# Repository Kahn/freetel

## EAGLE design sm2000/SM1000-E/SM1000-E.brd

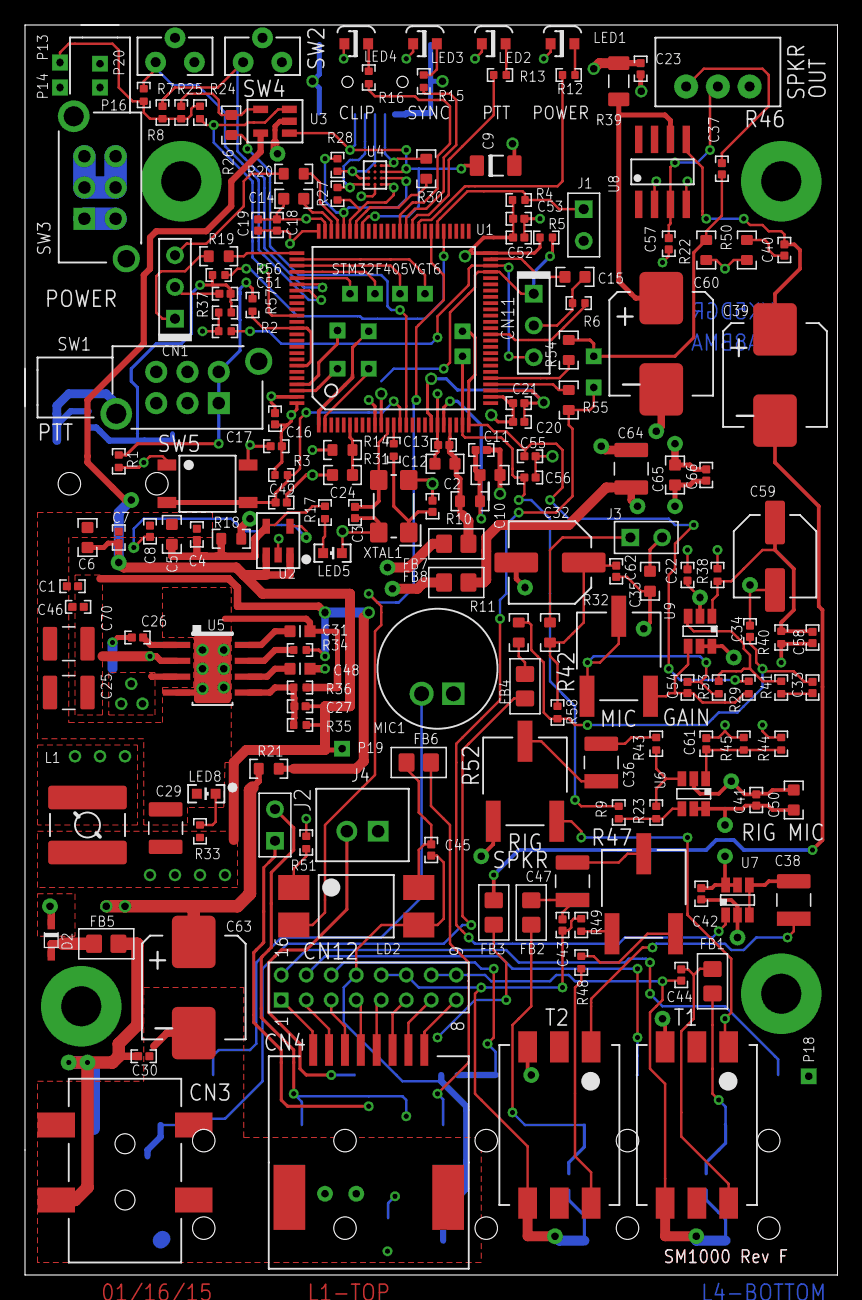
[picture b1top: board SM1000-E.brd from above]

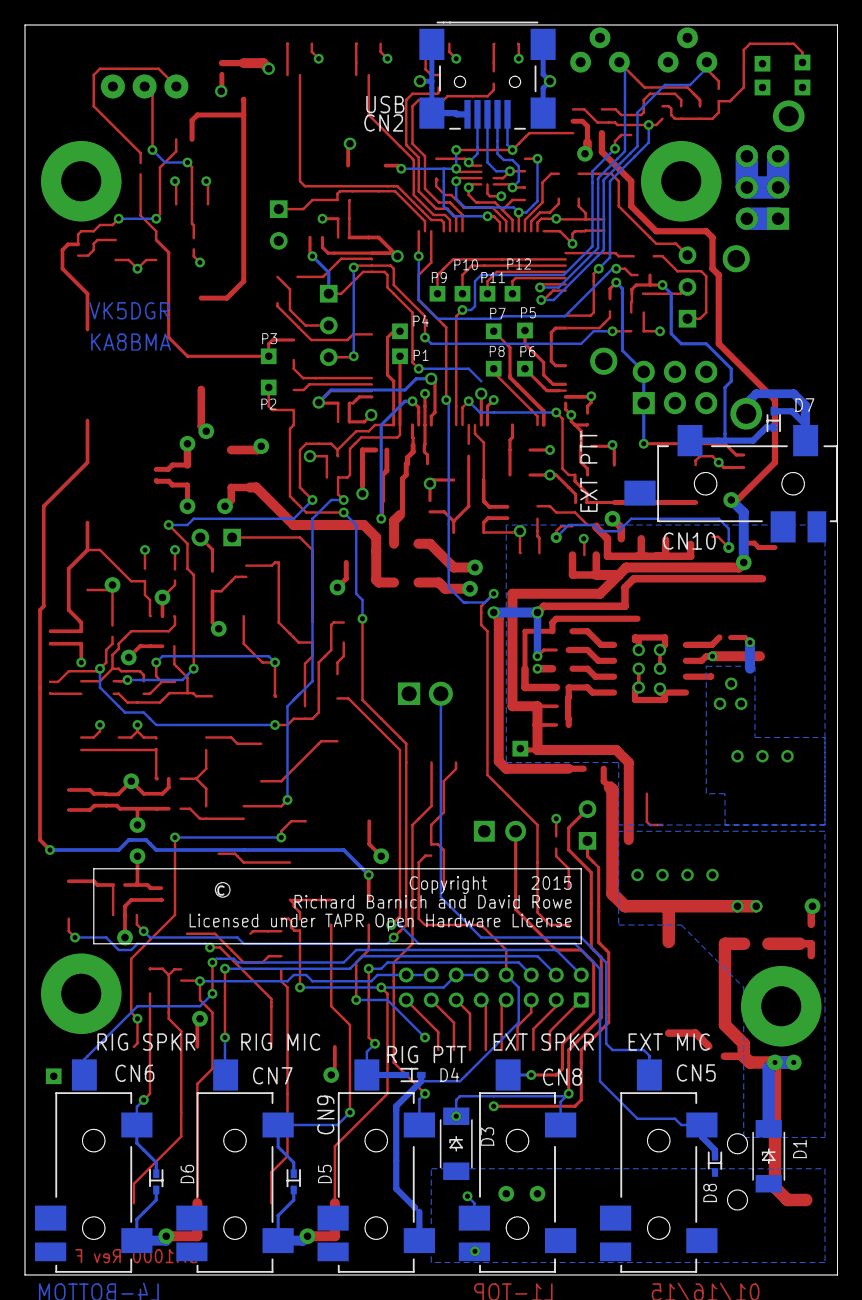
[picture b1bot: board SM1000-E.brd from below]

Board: 4 copper layers, 65.0 x 100.0 mm, 207 parts (26 on the bottom side), 128 nets.

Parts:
C1, C34, C55, C56: 1nF,25V,0402; CAPC1005X60N
C2, C3, C27: 20pF,50V; CAPC1005X60N
C4, C7, C11, C13, C16, C18, C20, C22, C23, C26, C37, C41, C42, C46, C49, C51, C52, C58, C61, C62, C66: 100nF,25V; CAPC1005X60N
C5, C6, C10, C12, C24, C65: 1uF,16V; CAPC1608X92N
C8, C17, C19, C21, C30, C53: 10nF,25V; CAPC1005X60N
C9: 4.7uF,16V,TANT; C1206-TANT
C14, C15, C35, C50: 2.2uF,16V; CAPC1608X92N
C25, C29, C64, C70: 22uF,25V,1210; CAPC3225X168N
C31: 8.2nF,25V; CAPC1608X92N
C32, C59: 100uF,6.3V,EL; NICHICON-WX-6.3
C33: 220nF,25V; CAPC1005X60N
C36, C38, C47: 100uF,10V; C1210
C39, C60, C63: 220uF,25V; CAP-CHEMI-HA0
C40: 47nF,25V; CAPC1005X60N
C43, C44, C45, C54: 100pF,50V; CAPC1005X60N
C48: 470nF,25V; CAPC1608X92N
C57: 3.9nF,16V,0402; CAPC1005X60N
CN1, CN11: HDR100-3
CN2: JS-MU3-002; JI-MU3-002
CN3: DS-0518
CN4: RJ-45; CONN-RJ45-MOLEX-44144-003
CN5, CN6, CN7, CN8, CN9, CN10: ST-3509
CN12: HRS-A3C-16DA
D1: PTVS20VP1UP; SOD128
D2: BAT60J; SOD323R_INFINEON
D3: DNL; SOD128
D4, D5, D6, D7, D8: DNL; SOD523
DRILEGEND: DRILEGEND
FB1, FB2, FB3, FB4, FB5, FB6, FB7, FB8: FB0805; FE0805
J1, J2, J3: JMP-2PIN; JMPR-2PIN
J4: CONN-BOOM-XH-2A
L1: 4.2uH; SRR5028
LD2: LTV-817S
LED1, LED3: LTST-S220KGKT; LTST-S2200K
LED2, LED4: LTST-S220KRKT; LTST-S2200K
LED5, LED8: DNL; SML-LX0603SRW
MIC1: CMA-4544PF-W
P1, P2, P3, P4, P5, P6, P7, P8, P9, P10, P11, P12, P13, P14, P16, P18, P19, P20: TPAD50
PCB1: SM1000D; NOPACKAGE
R1, R7, R8, R25, R34, R37, R43, R44, R45, R48: 10K,1%; RESC1005X40AN
R2, R3, R4, R5: 4.7K,1%; RESC1005X40AN
R6: 1K,1%; RESC1005X40AN
R9, R29: 1.5K,1%; RESC1005X40AN
R10: 47,1%; RESC1608X55N
R11, R32: 100,1%; RESC1608X55N
R12, R13, R15, R16: 680,1%; RESC1005X40AN
R14: 220,1%; RESC1005X40AN
R17, R33: DNL; RESC1005X40AN
R18, R21, R26, R30, R31, R54, R55: 0 Ohm; RESC1608X55N
R19, R20: 22,1%; RESC1608X55N
R22: 22.1K,1%; RESC1608X55N
R23, R24: 47K,1%; RESC1005X40AN
R27, R28: 22,1%; RESC1005X40AN
R35: 124.0K,1%; RESC1005X40AN
R36: 22.1K,1%; RESC1005X40AN
R38, R40, R41, R53, R56, R58: 2.2K,1%; RESC1005X40AN
R39: 4.7,0.5W,1206; RESC3115X70N
R42: 500K,TrimPOT; POT3361
R46: 100K,POT; POT-3310C
R47: 500,TrimPOT; POT3361
R49: 4.7,1%; RESC1005X40AN
R50: 10,1%; RESC1608X55N
R51: 390,1%; RESC1005X40AN
R52: 1K,TrimPOT; POT3361
R57: 470,1%; RESC1005X40AN
SH1, SH2, SH3: SHUNT,0.1IN; NOPACKAGE
SPKR1: SPKR-HY4004M-001; NOPACKAGE
SW1: SW-LC2259
SW2, SW4: TS-026
SW3: SW-LC2259EENP; SW-LC2259
SW5: TS-02B
T1, T2: SM-LP-5001
U1: STM32F405VGT6; LQFP100-14
U2: LD3985M33R; SOT23-5L
U3: STMPS2141; SOT23-5L
U4: EMIF02-USB03F2; ECOPACK-11
U5: TPS54329E; PSO-DDA
U6, U7, U9: LMV341; SOT23-6
U8: LM386M-1; SO08
U$4: SWPS-OTL
XTAL1: XTAL-FY0800035

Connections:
!BACK!: R8.1, SW4.1, U1.82
!BOOT0!: R57.1, U1.88, U1.94
!CPPT!: LD2.2, U1.57
!EXT-PTT!: R56.2, U1.55
!SELECT!: R7.1, SW2.1, U1.81
!TEST!: J1.1, R4.2, U1.56
+3.3V: C4.1, C5.1, R17.2, R18.1, U2.5
+5V: C6.1, C7.1, C27.1, C29.1, L1.2, P19.1, R33.1, R35.1, U2.1, U2.3, U3.5
+VIN: C23.1, C63.1, P20.1, R21.1, R39.1, SW3.2, SW3.3, SW3.5, SW3.6
AIN1: C56.1, P1.1, R9.1, U1.24
AIN2: C55.1, P4.1, R29.1, U1.25
APTT: CN9.D, CN12.14, D4.C
AVDD: C22.1, C35.1, C41.1, C42.1, C50.1, C64.1, C65.1, C66.1, FB8.2, J3.2, R38.2, R44.2, U6.5, U6.6, U7.5, U7.6, U9.5, U9.6
BOOT1: R6.2, U1.37
DAC1_OUT: P2.1, R55.2, U7.1
DAC2_OUT: C37.1, P3.1, R22.1, R54.2
GND: C1.1, C2.2, C3.2, C4.2, C5.2, C6.2, C7.2, C8.2, C9.2, C10.2, C11.2, C12.2, C13.2, C14.2, C15.2, C16.2, C17.2, C18.2, C19.2, C20.2, C21.2, C22.2, C23.2, C24.2, C25.2, C29.2, C30.2, C31.2, C32.2, C34.2, C35.2, C41.2, C42.2, C46.2, C48.2, C49.2, C50.2, C51.2, C52.2, C53.2, C55.2, C56.2, C57.2, C58.1, C59.2, C60.2, C61.2, C62.2, C63.2, C64.2, C65.2, C66.2, C70.2, CN1.2, CN2.5, CN2.6, CN2.7, CN2.8, CN2.9, CN3.2, CN4.9, CN4.10, CN5.A, CN8.A, CN10.A, CN11.2, D1.A, D3.A, D7.A, D8.A, J1.2, J4.1, LED1.C, LED2.C, LED3.C, LED4.C, LED5.C, LED8.C, MIC1.2, P14.1, P16.1, P18.1, R1.1, R6.1, R22.2, R36.2, R40.2, R45.2, R46.1, R50.2, R52.1, SW1.7, SW1.8, SW2.2, SW2.3, SW3.7, SW3.8, SW4.2, SW4.3, SW5.1, SW5.2, T1.3, T2.3, U1.10, U1.20, U1.27, U1.74, U1.99, U2.2, U3.2, U4.D2, U5.4, U5.EP, U6.2, U7.2, U8.2, U8.4, U9.2, XTAL1.2, XTAL1.4
LED-ERR: R16.1, U1.62
LED-PTT: R13.1, U1.60
LED-PWR: R12.1, U1.59
LED-RT: R15.1, U1.61
MIC: CN7.D, CN12.15
MISO: P11.1, U1.79
MOSI: P12.1, U1.80
unnamed: C14.1, U1.73
unnamed: C24.1, R31.2, U1.6
unnamed: C15.1, U1.49
unnamed: C10.1, C11.1, R10.2, U1.21
unnamed: C12.1, C13.1, FB7.2, R10.1, U1.22
unnamed: CN1.3, R20.2
unnamed: CN1.1, R19.2
unnamed: C39.1, C40.1, U8.5
unnamed: C36.2, R52.2
unnamed: C2.1, R14.2, XTAL1.1
unnamed: R55.1, U1.29
unnamed: C8.1, U2.4
unnamed: R54.1, U1.30
unnamed: R1.2, R57.2, SW1.1, SW1.4
unnamed: C51.1, CN10.C, D7.C, R37.2, R56.1
unnamed: LED1.A, R12.2
unnamed: LED2.A, R13.2
unnamed: LED3.A, R15.2
unnamed: LED5.A, R17.1
unnamed: LED4.A, R16.2
unnamed: C26.1, U5.1
unnamed: CN2.3, R28.1, U4.C1
unnamed: CN2.2, R27.1, U4.D1
unnamed: D2.A, FB5.2
unnamed: C33.1, C34.1, R11.2, R58.1
unnamed: FB4.2, R11.1
unnamed: C54.2, R29.2, R42.3, U9.4
unnamed: CN2.4, R30.1, U4.A3
unnamed: J3.1, R32.2
unnamed: C27.2, R35.2, R36.1, U5.5
unnamed: R25.1, R26.2, U3.4
unnamed: R23.2, R43.1, U6.3
unnamed: C44.1, FB1.1, T1.6
unnamed: C37.2, R46.3
unnamed: C33.2, R41.1
unnamed: C1.2, C25.1, C46.1, C70.1, R21.2, R34.1, U5.2
unnamed: R9.2, R23.1, U6.4
unnamed: C31.1, U5.8
unnamed: C57.1, R46.2, U8.3
unnamed: C48.1, U5.6
unnamed: C54.1, R42.1, R42.2, R53.2
unnamed: R34.2, U5.7
unnamed: C40.2, R50.1
unnamed: C39.2, FB3.1
unnamed: C32.1, C62.1, R32.1, R58.2
unnamed: C58.2, C59.1, R38.1, R40.1, U9.1
unnamed: LED8.A, R33.2
unnamed: C60.1, R39.2, U8.6
unnamed: LD2.1, R51.1
unnamed: C36.1, R43.2
unnamed: CN4.8, CN12.8
unnamed: CN4.7, CN12.7
unnamed: CN4.6, CN12.6
unnamed: CN4.5, CN12.5
unnamed: CN4.4, CN12.4
unnamed: CN4.3, CN12.3
unnamed: CN4.2, CN12.2
unnamed: CN4.1, CN12.1
unnamed: C61.1, R44.1, R45.1, U6.1
unnamed: CN5.D, MIC1.1
unnamed: R47.1, R49.2
unnamed: CN8.C, D3.C, FB3.2, J2.2
unnamed: R52.3, T1.1
unnamed: CN8.B, J2.1
unnamed: C38.2, T2.1
unnamed: CN7.C, D5.C, FB2.2
unnamed: C38.1, U7.3, U7.4
unnamed: CN8.D, J4.2
unnamed: CN9.C, FB6.2
unnamed: C45.1, FB6.1, LD2.4
unnamed: CN5.C, D8.C, FB4.1
unnamed: C30.1, CN3.1, D1.C, FB5.1
unnamed: R48.2, T2.6
unnamed: C43.1, C47.2, FB2.1
unnamed: C47.1, R47.2
unnamed: D2.C, SW3.1, SW3.4
unnamed: R47.3, R48.1
unnamed: CN6.C, D6.C, FB1.2
unnamed: R41.2, R53.1, U9.3
NRST: C49.1, R3.2, SW5.3, SW5.4, U1.14
NSS: P9.1, U1.77
OSC_IN: C3.1, U1.12, XTAL1.3
OSC_OUT: R14.1, U1.13
OTG_DM: R27.2, U1.70, U4.D3
OTG_DP: R28.2, U1.71, U4.C3
OTG_ID: R30.2, U1.69
OTG_OVR_CUR: R24.2, U1.86, U3.3
OTG_PWR_ON: R26.1, U1.15
PE0: P5.1, U1.97
PE1: P6.1, U1.98
PE2: P7.1, U1.1
PE3: P8.1, U1.2
RF_MIC: C43.2, CN7.A, CN12.11, CN12.12, D5.A, R49.1, T2.4
RF_PTT: C45.2, CN9.A, CN12.13, D4.A, LD2.3
RF_SPKR: C44.2, CN6.A, CN12.9, CN12.10, D6.A, T1.4
SCK: P10.1, U1.78
SPKR: CN6.D, CN12.16
SW: C26.2, L1.1, U5.3
SWCLK: R19.1, U1.76
SWDIO: R20.1, U1.72
USART3_RX: CN11.3, R2.2, U1.48
USART3_TX: CN11.1, R5.2, U1.47
VBUS: C9.1, CN2.1, U1.68, U3.1, U4.B3
VDD: C16.1, C17.1, C18.1, C19.1, C20.1, C21.1, C52.1, C53.1, FB7.1, FB8.1, P13.1, R2.1, R3.1, R4.1, R5.1, R7.2, R8.2, R18.2, R24.1, R25.2, R31.1, R37.1, R51.2, SW1.2, SW1.5, U1.11, U1.19, U1.28, U1.50, U1.75, U1.100

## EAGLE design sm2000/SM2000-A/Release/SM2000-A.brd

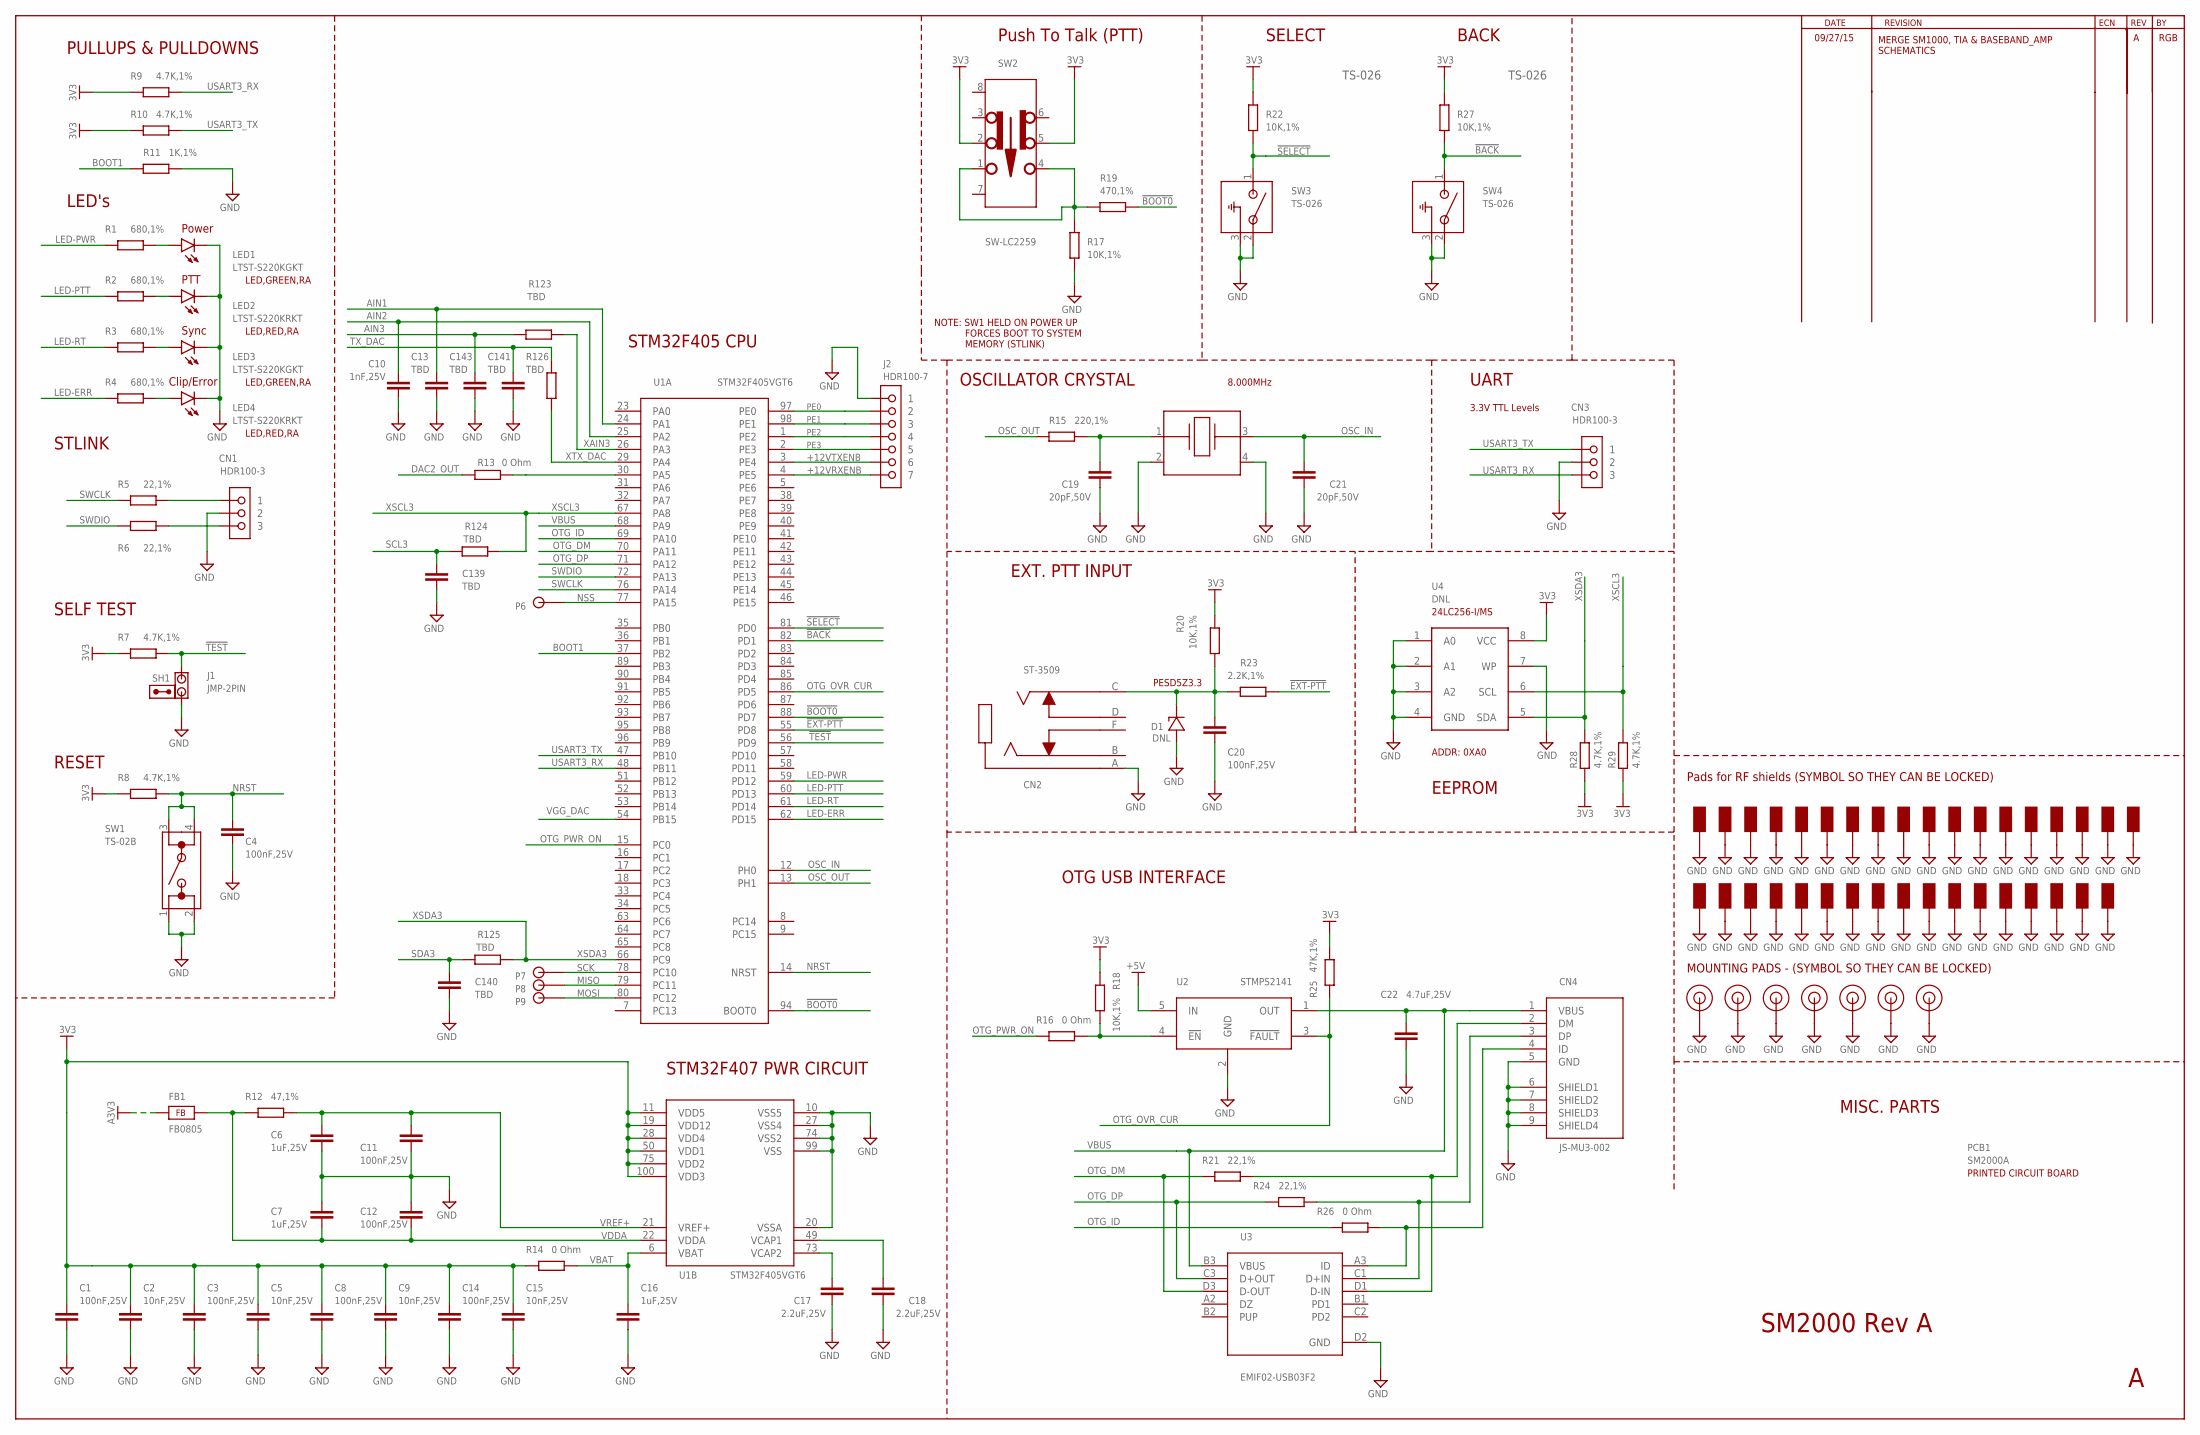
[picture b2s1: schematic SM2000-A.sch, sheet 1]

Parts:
C1, C3, C4, C8, C11, C12, C14, C20: 100nF,25V; C0805
C2, C5, C9, C15: 10nF,25V; C0805
C6, C7, C16: 1uF,25V; C0805
C10: 1nF,25V; C0805
C13, C139, C140, C141, C143: TBD; C0805
C17, C18: 2.2uF,25V; C0805
C19, C21: 20pF,50V; C0805
C22: 4.7uF,25V; C0805
CN1, CN3: HDR100-3
CN2: ST-3509
CN4: JS-MU3-002; JI-MU3-002
D1: DNL; SOD523
FB1: FB0805; FE0805
J1: JMP-2PIN; JMPR-2PIN
J2: HDR100-7
LED1, LED3: LTST-S220KGKT; LTST-S2200K
LED2, LED4: LTST-S220KRKT; LTST-S2200K
P6, P7, P8, P9: TPAD50
PAD1, PAD2, PAD3, PAD4, PAD5, PAD6, PAD7: MTG-PAD-3.2
PCB1: SM2000A; NOPACKAGE
R1, R2, R3, R4: 680,1%; R0805
R5, R6, R21, R24: 22,1%; R0805
R7, R8, R9, R10, R28, R29: 4.7K,1%; R0805
R11: 1K,1%; R0805
R12: 47,1%; R0805
R13, R14, R16, R26: 0 Ohm; R0805
R15: 220,1%; R0805
R17, R18, R20, R22, R27: 10K,1%; R0805
R19: 470,1%; R0805
R23: 2.2K,1%; R0805
R25: 47K,1%; R0805
R123, R124, R125, R126: TBD; R0805
S1, S2, S3, S4, S5, S6, S8, S9, S10, S11, S12, S14, S15, S16, S17, S18, S20, S21, S22, S23, S24, S25, S26, S27, S28, S29, S30, S31, S35, S36, S37, S38, S39, S40, S43: SGND
SH1: SHUNT,0.1IN; NOPACKAGE
SW1: TS-02B
SW2: SW-LC2259
SW3, SW4: TS-026
U1: STM32F405VGT6; LQFP100-14
U2: STMPS2141; SOT23-5L
U3: EMIF02-USB03F2; ECOPACK-11
U4: DNL; SOIC8
XTAL1: 8.000MHz; CTS-405

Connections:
3V3: C1.1, C2.1, C3.1, C5.1, C8.1, C9.1, C14.1, C15.1, R7.1, R8.1, R9.1, R10.1, R14.1, R18.2, R20.1, R22.2, R25.1, R27.2, R28.1, R29.1, SW2.2, SW2.5, U1.11 (VDD5), U1.19 (VDD12), U1.28 (VDD4), U1.50 (VDD1), U1.75 (VDD2), U1.100 (VDD3), U4.8 (VCC); also elsewhere on the board
!BACK!: R27.1, SW4.1, U1.82 (PD1)
!BOOT0!: R19.1, U1.88 (PD7), U1.94 (BOOT0)
!EXT-PTT!: R23.2, U1.55 (PD8)
!SELECT!: R22.1, SW3.1, U1.81 (PD0)
!TEST!: J1.1, R7.2, U1.56 (PD9)
+5V: U2.5 (IN); also elsewhere on the board
+12VRXENB: J2.7, U1.4 (PE5); also elsewhere on the board
+12VTXENB: J2.6, U1.3 (PE4); also elsewhere on the board
A3V3: FB1.1; also elsewhere on the board
AIN1: C13.1, U1.24 (PA1); also elsewhere on the board
AIN2: C10.1, U1.25 (PA2); also elsewhere on the board
AIN3: C143.1, R123.2; also elsewhere on the board
BOOT1: R11.2, U1.37 (PB2)
DAC2_OUT: R13.2; also elsewhere on the board
GND: C1.2, C2.2, C3.2, C4.2, C5.2, C6.2, C7.2, C8.2, C9.2, C10.2, C11.2, C12.2, C13.2, C14.2, C15.2, C16.2, C17.2, C18.2, C19.2, C20.2, C21.2, C22.2, C139.2, C140.2, C141.2, C143.2, CN1.2, CN2.A, CN3.2, CN4.5 (GND), CN4.6 (SHIELD1), CN4.7 (SHIELD2), CN4.8 (SHIELD3), CN4.9 (SHIELD4), D1.A, J1.2, J2.1, LED1.C, LED2.C, LED3.C, LED4.C, PAD1.P$1, PAD2.P$1, PAD3.P$1, PAD4.P$1, PAD5.P$1, PAD6.P$1, PAD7.P$1, R11.1, R17.1, S1.1, S2.1, S3.1, S4.1, S5.1, S6.1, S8.1, S9.1, S10.1, S11.1, S12.1, S14.1, S15.1, S16.1, S17.1, S18.1, S20.1, S21.1, S22.1, S23.1, S24.1, S25.1, S26.1, S27.1, S28.1, S29.1, S30.1, S31.1, S35.1, S36.1, S37.1, S38.1, S39.1, S40.1, S43.1, SW1.1, SW1.2, SW3.2, SW3.3, SW4.2, SW4.3, U1.10 (VSS5), U1.20 (VSSA), U1.27 (VSS4), U1.74 (VSS2), U1.99 (VSS), U2.2 (GND), U3.D2 (GND), U4.1 (A0), U4.2 (A1), U4.3 (A2), U4.4 (GND), U4.7 (WP), XTAL1.2, XTAL1.4; also elsewhere on the board
LED-ERR: R4.1, U1.62 (PD15)
LED-PTT: R2.1, U1.60 (PD13)
LED-PWR: R1.1, U1.59 (PD12)
LED-RT: R3.1, U1.61 (PD14)
MISO: P8.1, U1.79 (PC11)
MOSI: P9.1, U1.80 (PC12)
unnamed: C17.1, U1.73 (VCAP2)
unnamed: C18.1, U1.49 (VCAP1)
unnamed: CN1.3, R6.2
unnamed: CN1.1, R5.2
unnamed: C19.1, R15.2, XTAL1.1
unnamed: R13.1, U1.30 (PA5)
unnamed: R17.2, R19.2, SW2.1, SW2.4
unnamed: C20.1, CN2.C, D1.C, R20.2, R23.1
unnamed: LED1.A, R1.2
unnamed: LED2.A, R2.2
unnamed: LED3.A, R3.2
unnamed: LED4.A, R4.2
unnamed: CN4.3 (DP), R24.1, U3.C1 (D+IN)
unnamed: CN4.2 (DM), R21.1, U3.D1 (D-IN)
unnamed: CN4.4 (ID), R26.1, U3.A3 (ID)
unnamed: R16.2, R18.1, U2.4 (!EN!)
NRST: C4.1, R8.2, SW1.3, SW1.4, U1.14 (NRST)
NSS: P6.1, U1.77 (PA15)
OSC_IN: C21.1, U1.12 (PH0), XTAL1.3
OSC_OUT: R15.1, U1.13 (PH1)
OTG_DM: R21.2, U1.70 (PA11), U3.D3 (D-OUT)
OTG_DP: R24.2, U1.71 (PA12), U3.C3 (D+OUT)
OTG_ID: R26.2, U1.69 (PA10)
OTG_OVR_CUR: R25.2, U1.86 (PD5), U2.3 (!FAULT!)
OTG_PWR_ON: R16.1, U1.15 (PC0)
PE0: J2.2, U1.97 (PE0)
PE1: J2.3, U1.98 (PE1)
PE2: J2.4, U1.1 (PE2)
PE3: J2.5, U1.2 (PE3)
SCK: P7.1, U1.78 (PC10)
SCL3: C139.1, R124.2; also elsewhere on the board
SDA3: C140.1, R125.2; also elsewhere on the board
SWCLK: R5.1, U1.76 (PA14)
SWDIO: R6.1, U1.72 (PA13)
TX_DAC: C141.1, R126.2; also elsewhere on the board
USART3_RX: CN3.3, R9.2, U1.48 (PB11)
USART3_TX: CN3.1, R10.2, U1.47 (PB10)
VBAT: C16.1, R14.2, U1.6 (VBAT)
VBUS: C22.1, CN4.1 (VBUS), U1.68 (PA9), U2.1 (OUT), U3.B3 (VBUS)
VDDA: C7.1, C12.1, FB1.2, R12.1, U1.22 (VDDA)
VGG_DAC: U1.54 (PB15); also elsewhere on the board
VREF+: C6.1, C11.1, R12.2, U1.21 (VREF+)
XAIN3: R123.1, U1.26 (PA3)
XSCL3: R29.2, R124.1, U1.67 (PA8), U4.6 (SCL)
XSDA3: R28.2, R125.1, U1.66 (PC9), U4.5 (SDA)
XTX_DAC: R126.1, U1.29 (PA4)

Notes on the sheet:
PULLUPS & PULLDOWNS
LED's
STLINK
OSCILLATOR CRYSTAL
OTG USB INTERFACE
STM32F405 CPU
STM32F407 PWR CIRCUIT
SM2000 Rev A
Push To Talk (PTT)
NOTE: SW1 HELD ON POWER UP FORCES BOOT TO SYSTEM MEMORY (STLINK)
SELF TEST
RESET
SELECT
BACK
Power
PTT
Sync
Clip/Error
UART
3.3V TTL Levels
8.000MHz
TS-026
RGB
MISC. PARTS
LED,GREEN,RA
LED,RED,RA
EEPROM
ADDR: 0XA0
09/27/15
24LC256-I/MS
MERGE SM1000, TIA & BASEBAND_AMP SCHEMATICS
EXT. PTT INPUT
PESD5Z3.3
Pads for RF shields (SYMBOL SO THEY CAN BE LOCKED)
MOUNTING PADS - (SYMBOL SO THEY CAN BE LOCKED)

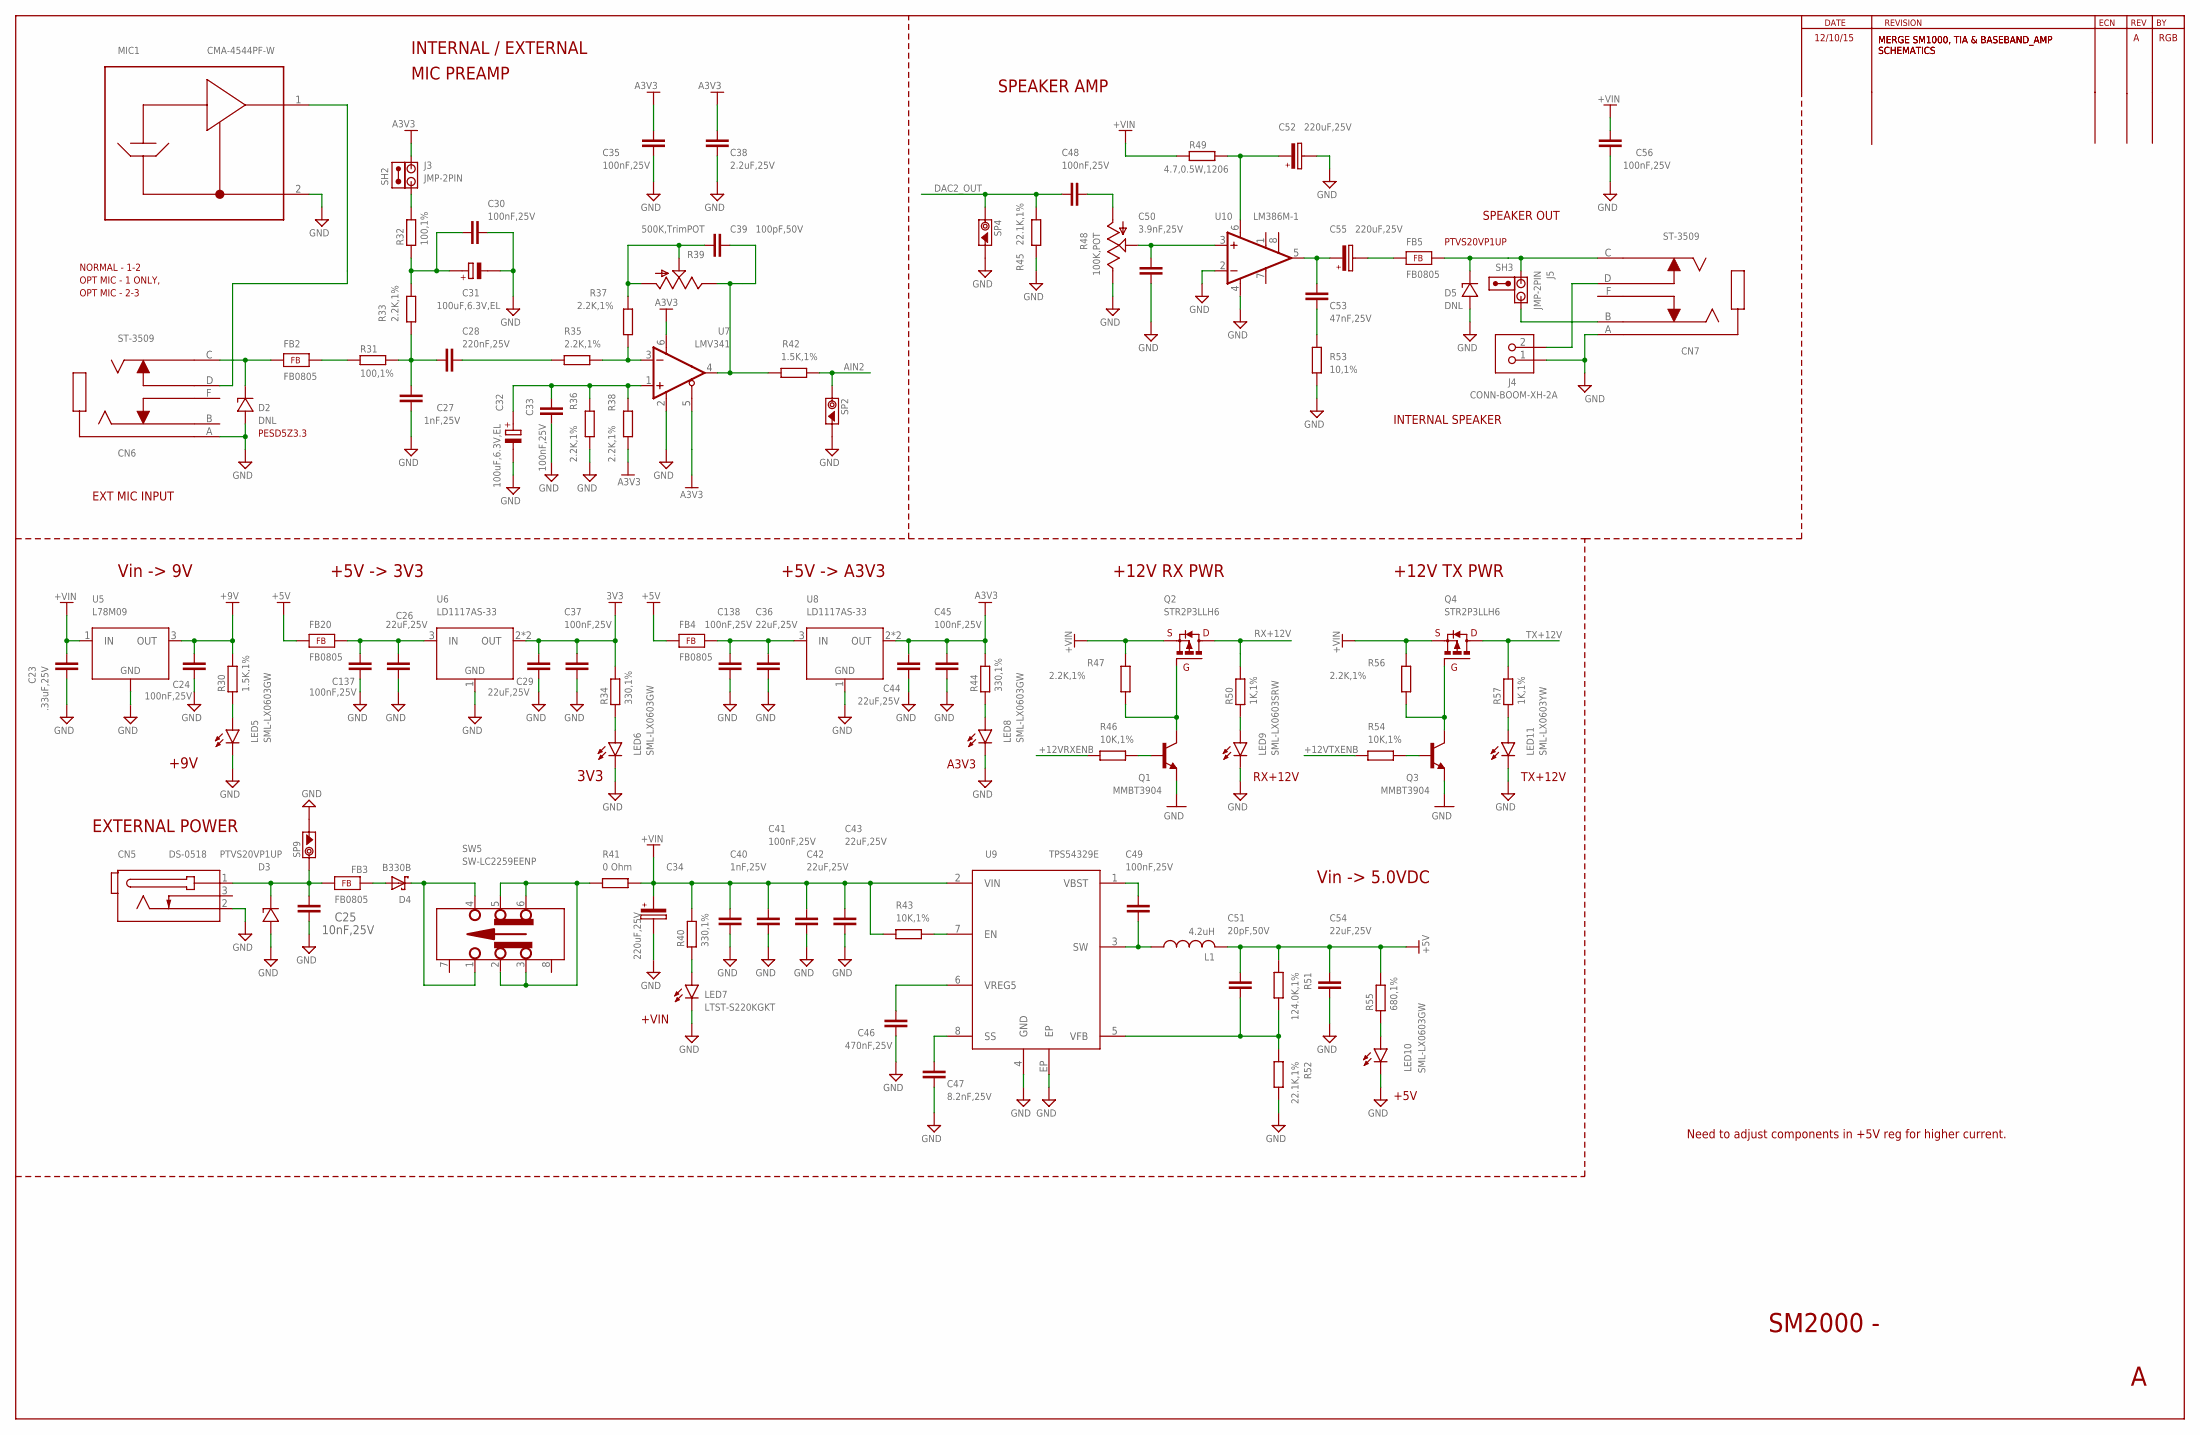
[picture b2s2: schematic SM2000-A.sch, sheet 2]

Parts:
C23: .33uF,25V; C0805
C24, C30, C33, C35, C37, C41, C45, C48, C49, C56, C137, C138: 100nF,25V; C0805
C25: 10nF,25V; C0805
C26, C29, C36, C42, C43, C44, C54: 22uF,25V; C1210
C27, C40: 1nF,25V; C0805
C28: 220nF,25V; C0805
C31, C32: 100uF,6.3V,EL; NICHICON-WX-6.3
C34, C52, C55: 220uF,25V; CAP-CHEMI-HA0
C38: 2.2uF,25V; C0805
C39: 100pF,50V; C0805
C46: 470nF,25V; C0805
C47: 8.2nF,25V; C0805
C50: 3.9nF,25V; C0805
C51: 20pF,50V; C0805
C53: 47nF,25V; C0805
CN5: DS-0518
CN6, CN7: ST-3509
D2: DNL; SOD523
D3: PTVS20VP1UP; SOD128
D4: B330B; SMB
D5: DNL; SOD128
FB2, FB3, FB4, FB5, FB20: FB0805; FE0805
J3, J5: JMP-2PIN; JMPR-2PIN
J4: CONN-BOOM-XH-2A
L1: 4.2uH; SRR5028
LED5, LED6, LED8, LED10: SML-LX0603GW; SML-LX0603SRW
LED7: LTST-S220KGKT; LTST-S2200K
LED9: SML-LX0603SRW
LED11: SML-LX0603YW; SML-LX0603SRW
MIC1: CMA-4544PF-W
Q1, Q3: MMBT3904; SOT23
Q2, Q4: STR2P3LLH6; SOT23
R30, R42: 1.5K,1%; R0805
R31, R32: 100,1%; R0805
R33, R35, R36, R37, R38, R47, R56: 2.2K,1%; R0805
R34, R40, R44: 330,1%; R0805
R39: 500K,TrimPOT; POT3361
R41: 0 Ohm; R0805
R43, R46, R54: 10K,1%; R0805
R45, R52: 22.1K,1%; R0805
R48: 100K,POT; POT-3310C
R49: 4.7,0.5W,1206; R1206
R50, R57: 1K,1%; R0805
R51: 124.0K,1%; R0805
R53: 10,1%; R0805
R55: 680,1%; R0805
SH2, SH3: SHUNT,0.1IN; NOPACKAGE
SP2, SP4, SP9: SCOPE_PAD
SW5: SW-LC2259EENP; SW-LC2259
U5: L78M09; DPAK
U6, U8: LD1117AS-33; SOT223
U7: LMV341; SOT23-6
U9: TPS54329E; PSO-DDA
U10: LM386M-1; SO08

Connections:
3V3: C29.1, C37.1, R34.2, U6.2 (OUT), U6.4 (OUT); also elsewhere on the board
+5V: C51.1, C54.1, FB4.1, FB20.1, L1.2, R51.1, R55.2; also elsewhere on the board
+9V: C24.1, R30.2, U5.3 (OUT); also elsewhere on the board
+12VRXENB: R46.1; also elsewhere on the board
+12VTXENB: R54.1; also elsewhere on the board
+VIN: C23.1, C34.1, C40.1, C41.1, C42.1, C43.1, C56.1, Q2.2 (S), Q4.2 (S), R40.2, R41.2, R43.1, R47.2, R49.1, R56.2, U5.1 (IN), U9.2 (VIN)
A3V3: C35.1, C38.1, C44.1, C45.1, J3.2, R38.2, R44.2, U7.5 (!SHDN!), U7.6 (V+), U8.2 (OUT), U8.4 (OUT); also elsewhere on the board
AIN2: R42.1, SP2.1; also elsewhere on the board
DAC2_OUT: C48.1, R45.1, SP4.1; also elsewhere on the board
GND: C23.2, C24.2, C25.2, C26.2, C27.2, C29.2, C30.2, C31.2 (-), C32.2 (-), C33.1, C34.2, C35.2, C36.2, C37.2, C38.2, C40.2, C41.2, C42.2, C43.2, C44.2, C45.2, C46.2, C47.2, C50.2, C52.2, C54.2, C56.2, C137.2, C138.2, CN5.2, CN6.A, CN7.A, D2.A, D3.A, D5.A, J4.1, LED5.C, LED6.C, LED7.C, LED8.C, LED9.C, LED10.C, LED11.C, MIC1.2, Q1.2 (E), Q3.2 (E), R36.2, R45.2, R48.1, R52.2, R53.2, SP2.2, SP4.2, SP9.2, U5.4 (GND), U6.1 (GND), U7.2 (GND), U8.1 (GND), U9.4 (GND), U9.EP, U10.2 (-IN), U10.4 (GND); also elsewhere on the board
unnamed: C53.1, C55.1, U10.5 (OUT)
unnamed: D4.A, FB3.2
unnamed: C27.1, C28.1, R31.2, R33.1
unnamed: FB2.2, R31.1
unnamed: C39.2, R39.1, R42.2, U7.4 (OUT)
unnamed: J3.1, R32.2
unnamed: C48.2, R48.3
unnamed: C28.2, R35.1
unnamed: C50.1, R48.2, U10.3 (+IN)
unnamed: C39.1, R37.2, R39.2, R39.3
unnamed: Q1.3 (C), Q2.1 (G), R47.1
unnamed: C53.2, R53.1
unnamed: C55.2, FB5.1
unnamed: C30.1, C31.1 (+), R32.1, R33.2
unnamed: C32.1 (+), C33.2, R36.1, R38.1, U7.1 (+IN)
unnamed: C52.1, R49.2, U10.6 (VS)
unnamed: Q3.3 (C), Q4.1 (G), R56.1
unnamed: Q1.1 (B), R46.2
unnamed: C36.1, C138.1, FB4.2, U8.3 (IN)
unnamed: Q3.1 (B), R54.2
unnamed: CN6.D, MIC1.1
unnamed: CN7.C, D5.C, FB5.2, J5.2
unnamed: LED5.A, R30.1
unnamed: CN7.B, J5.1
unnamed: CN7.D, J4.2
unnamed: CN6.C, D2.C, FB2.1
unnamed: C25.1, CN5.1, D3.C, FB3.1, SP9.1
unnamed: D4.C (K), SW5.1, SW5.4
unnamed: R35.2, R37.1, U7.3 (-IN)
unnamed: C26.1, C137.1, FB20.2, U6.3 (IN)
unnamed: LED8.A, R44.1
unnamed: LED9.A, R50.1
unnamed: LED6.A, R34.1
unnamed: LED11.A, R57.1
unnamed: LED10.A, R55.1
unnamed: LED7.A, R40.1
unnamed: R41.1, SW5.2, SW5.3, SW5.5, SW5.6
unnamed: C49.1, U9.1 (VBST)
unnamed: C51.2, R51.2, R52.1, U9.5 (VFB)
unnamed: C47.1, U9.8 (SS)
unnamed: C46.1, U9.6 (VREG5)
unnamed: R43.2, U9.7 (EN)
RX+12V: Q2.3 (D), R50.2; also elsewhere on the board
SW: C49.2, L1.1, U9.3 (SW)
TX+12V: Q4.3 (D), R57.2; also elsewhere on the board

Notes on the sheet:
SPEAKER OUT
EXT MIC INPUT
EXTERNAL POWER
INTERNAL / EXTERNAL
MIC PREAMP
SPEAKER AMP
SM2000 -
NORMAL - 1-2
OPT MIC - 1 ONLY,
OPT MIC - 2-3
INTERNAL SPEAKER
+5V -> A3V3
PTVS20VP1UP
PESD5Z3.3
RGB
12/10/15
MERGE SM1000, TIA & BASEBAND_AMP SCHEMATICS
+12V RX PWR
+12V TX PWR
Vin -> 5.0VDC
+5V -> 3V3
Vin -> 9V
Need to adjust components in +5V reg for higher current.
+9V
3V3
A3V3
RX+12V
TX+12V
+5V
+VIN

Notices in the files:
sm2000/SM1000-E/SM1000-E.brd:
Copyright 2015
Licensed under TAPR Open Hardware License
parts and their libraries:
_RoweTel: Licensed Under the TAPR Open Hardware License(www.tapr.org/OHL)
_RoweTel: Copyright 2016  Richard Barnich and David Rowe
_RoweTel: Copyright 2014  Richard Barnich and David Rowe
